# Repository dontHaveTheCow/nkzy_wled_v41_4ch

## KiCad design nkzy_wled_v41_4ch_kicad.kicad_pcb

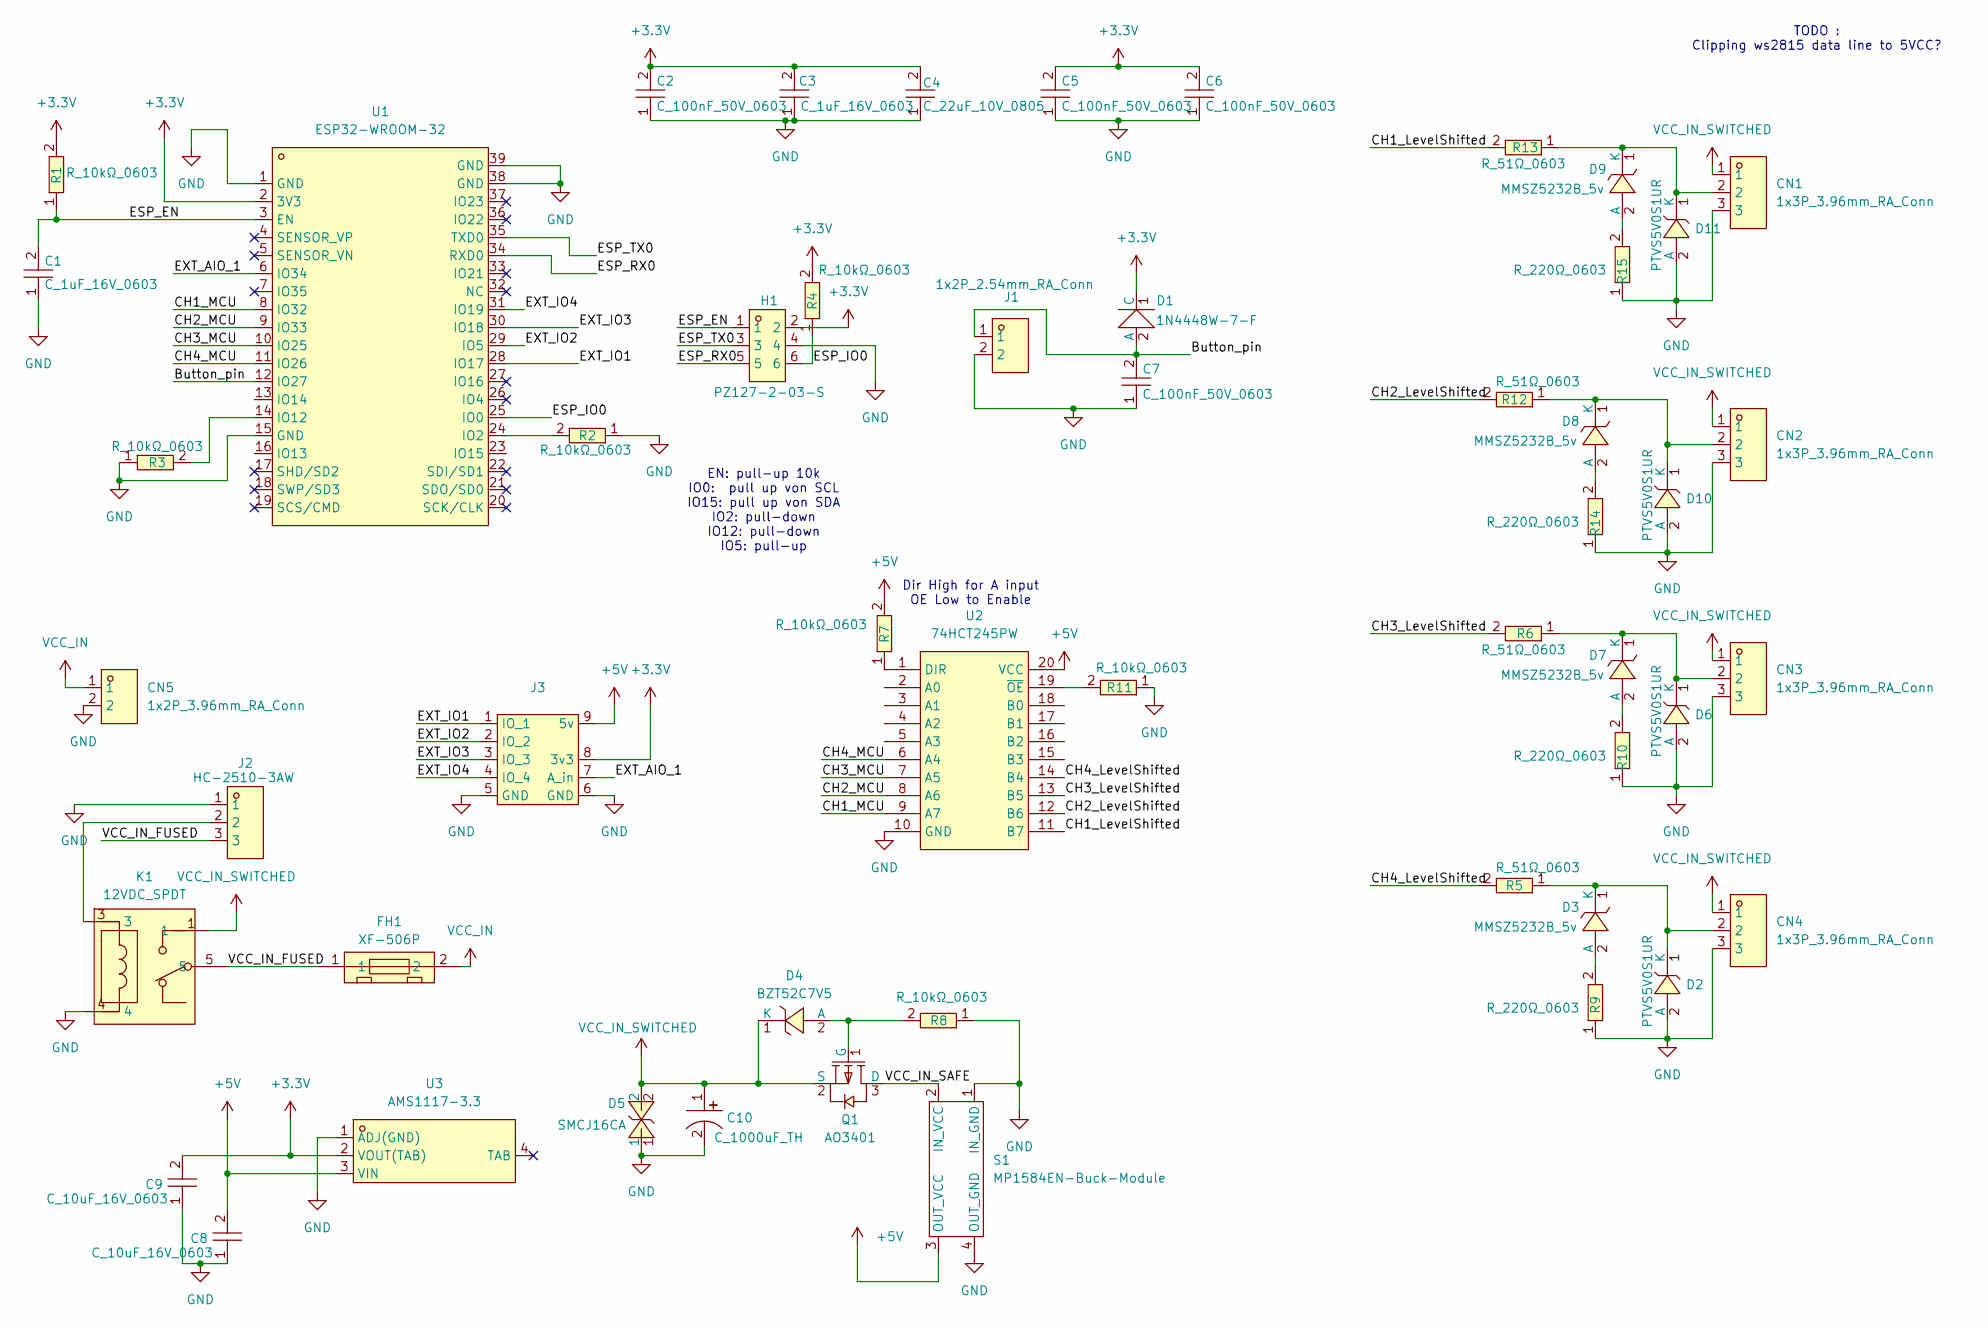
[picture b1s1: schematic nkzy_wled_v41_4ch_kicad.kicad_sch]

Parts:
C1, C3: C_1uF_16V_0603; C0603; Mfr. PartNo CL10A105KO8NNNC; LCSC Part C1592
C2, C5, C6, C7: C_100nF_50V_0603; C0603; Mfr. PartNo 0603B104K500NT; LCSC Part C30926
C4: C_22uF_10V_0805; C0805; Mfr. PartNo CL21A226MPQNNNE; LCSC Part C29277
C8, C9: C_10uF_16V_0603; C0603; Mfr. PartNo CL10A106MO8NQNC; LCSC Part C92487
C10: C_1000uF_TH; CAP-TH_BD10.0-P5.00-D1.0-FD; Mfr. PartNo 01EC4294SHC1000UF25V; LCSC Part C503217
CN1, CN2, CN3, CN4: 1x3P_3.96mm_RA_Conn; CONN-TH_3P-P3.96_HCTL_HC-VH-3A3W; Mfr. PartNo HC-VH-3A3W; LCSC Part C2845760
CN5: 1x2P_3.96mm_RA_Conn; CONN-TH_2P-P3.96_HCTL_HC-VH-2A2W-L; Mfr. PartNo HC-VH-2A2W-L; LCSC Part C2979575
D1: 1N4448W-7-F; SOD-123_L2.8-W1.8-LS3.7-RD; Mfr. PartNo 1N4448W-7-F; LCSC Part C124191
D2, D6, D10, D11: PTVS5V0S1UR; SOD-123FL_L2.7-W1.8-LS3.8-RD; Mfr. PartNo PTVS5V0S1UR; LCSC Part C5380694
D3, D7, D8, D9: MMSZ5232B_5v; SOD-123_L2.7-W1.6-LS3.7-RD; Mfr. PartNo MMSZ5232B; LCSC Part C19077423
D4: BZT52C7V5; SOD-123_L2.7-W1.6-LS3.7-RD; Mfr. PartNo BZT52C7V5; LCSC Part C19077405
D5: SMCJ16CA; DO-214AB_L6.9-W5.9-LS7.9-BI; Mfr. PartNo SMCJ16CA; LCSC Part C41411764
FH1: XF-506P; FUSE-TH_XF-506P; Mfr. PartNo XF-506P; LCSC Part C492610
H1: PZ127-2-03-S; HDR-SMD_6P-P1.27-V-M-R2-C3-LS5.3; Mfr. PartNo PZ127-2-03-S; LCSC Part C3975186
J1: 1x2P_2.54mm_RA_Conn; CONN-TH_2P-P2.54_HCTL_HC-2510-2AW; Mfr. PartNo HC-2510-2AW; LCSC Part C2982041
J2: HC-2510-3AW; CONN-TH_3P-P2.54_HCTL_HC-2510-3AW; Mfr. PartNo HC-2510-3AW; LCSC Part C2982042
J3: nkzy_addon_footprint
K1: 12VDC_SPDT; RELAY-TH_SRA-X-CX; Mfr. PartNo SRA-12VDC-CL; LCSC Part C60169
Q1: AO3401; SOT-23-3_L2.9-W1.4-P1.90-LS2.6-BR; Mfr. PartNo AO3401; LCSC Part C727156
R1, R2, R3, R4, R7, R8, R11: R_10kΩ_0603; R0603; Mfr. PartNo 0603WAF1002T5E; LCSC Part C25804
R5, R6, R12, R13: R_51Ω_0603; R0603; Mfr. PartNo 0603WAF510JT5E; LCSC Part C23197
R9, R10, R14, R15: R_220Ω_0603; R0603; Mfr. PartNo 0603WAF2200T5E; LCSC Part C22962
S1: MP1584EN-Buck-Module
U1: ESP32-WROOM-32; WIFIM-SMD_ESP32-WROOM-32-N4; Mfr. PartNo ESP32-WROOM-32; LCSC Part C82899
U2: 74HCT245PW; TSSOP-20_L6.5-W4.4-P0.65-LS6.4-BL; Mfr. PartNo 74HCT245PW; LCSC Part C5980
U3: AMS1117-3.3; SOT-223-4_L6.5-W3.5-P2.30-LS7.0-BR; Mfr. PartNo AMS1117-3.3_C347222; LCSC Part C347222

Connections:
+3.3V: C2.2, C3.2, C4.2, C5.2, C6.2, C9.2, D1.1 (C), H1.2, J3.8 (3v3), R1.2, R4.2, U1.2 (3V3), U3.2 (VOUT(TAB))
+5V: C8.2, J3.9 (5v), R7.2, S1.3 (OUT_VCC), U2.20 (VCC), U3.3 (VIN)
/Button_pin: C7.2, D1.2 (A), J1.1, U1.12 (IO27)
/CH1_LevelShifted: R13.2, U2.11 (B7)
/CH1_MCU: U1.8 (IO32), U2.9 (A7)
/CH2_LevelShifted: R12.2, U2.12 (B6)
/CH2_MCU: U1.9 (IO33), U2.8 (A6)
/CH3_LevelShifted: R6.2, U2.13 (B5)
/CH3_MCU: U1.10 (IO25), U2.7 (A5)
/CH4_LevelShifted: R5.2, U2.14 (B4)
/CH4_MCU: U1.11 (IO26), U2.6 (A4)
/ESP_EN: C1.2, H1.1, R1.1, U1.3 (EN)
/ESP_IO0: H1.6, R4.1, U1.25 (IO0)
/ESP_RX0: H1.5, U1.34 (RXD0)
/ESP_TX0: H1.3, U1.35 (TXD0)
/EXT_AIO_1: J3.7 (A_in), U1.6 (IO34)
/EXT_IO1: J3.1 (IO_1), U1.28 (IO17)
/EXT_IO2: J3.2 (IO_2), U1.29 (IO5)
/EXT_IO3: J3.3 (IO_3), U1.30 (IO18)
/EXT_IO4: J3.4 (IO_4), U1.31 (IO19)
/VCC_IN_FUSED: FH1.1, J2.3, K1.5
/VCC_IN_SAFE: Q1.3 (D), S1.2 (IN_VCC)
GND: C1.1, C2.1, C3.1, C4.1, C5.1, C6.1, C7.1, C8.1, C9.1, C10.2, CN1.3, CN2.3, CN3.3, CN4.3, CN5.2, D2.2 (A), D5.1, D6.2 (A), D10.2 (A), D11.2 (A), H1.4, J1.2, J2.1, J3.5 (GND), J3.6 (GND), K1.4, R2.1, R3.1, R8.1, R9.1, R10.1, R11.1, R14.1, R15.1, S1.1 (IN_GND), S1.4 (OUT_GND), U1.1 (GND), U1.15 (GND), U1.38 (GND), U1.39 (GND), U2.10 (GND), U3.1 (ADJ(GND))
unnamed: CN4.2, D2.1 (K), D3.1 (K), R5.1
unnamed: D3.2 (A), R9.2
unnamed: D4.2 (A), Q1.1 (G), R8.2
unnamed: CN3.2, D6.1 (K), D7.1 (K), R6.1
unnamed: D7.2 (A), R10.2
unnamed: D8.2 (A), R14.2
unnamed: D9.2 (A), R15.2
unnamed: CN2.2, D8.1 (K), D10.1 (K), R12.1
unnamed: CN1.2, D9.1 (K), D11.1 (K), R13.1
unnamed: J2.2, K1.3
unnamed: R2.2, U1.24 (IO2)
unnamed: R3.2, U1.14 (IO12)
unnamed: R7.1, U2.1 (DIR)
unnamed: R11.2, U2.19 (~OE)
VCC_IN: CN5.1, FH1.2
VCC_IN_SWITCHED: C10.1, CN1.1, CN2.1, CN3.1, CN4.1, D4.1 (K), D5.2, K1.1, Q1.2 (S)

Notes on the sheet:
Dir High for A input OE Low to Enable
TODO : Clipping ws2815 data line to 5VCC?
EN: pull-up 10k IO0: pull up von SCL IO15: pull up von SDA IO2: pull-down IO12: pull-down IO5: pull-up

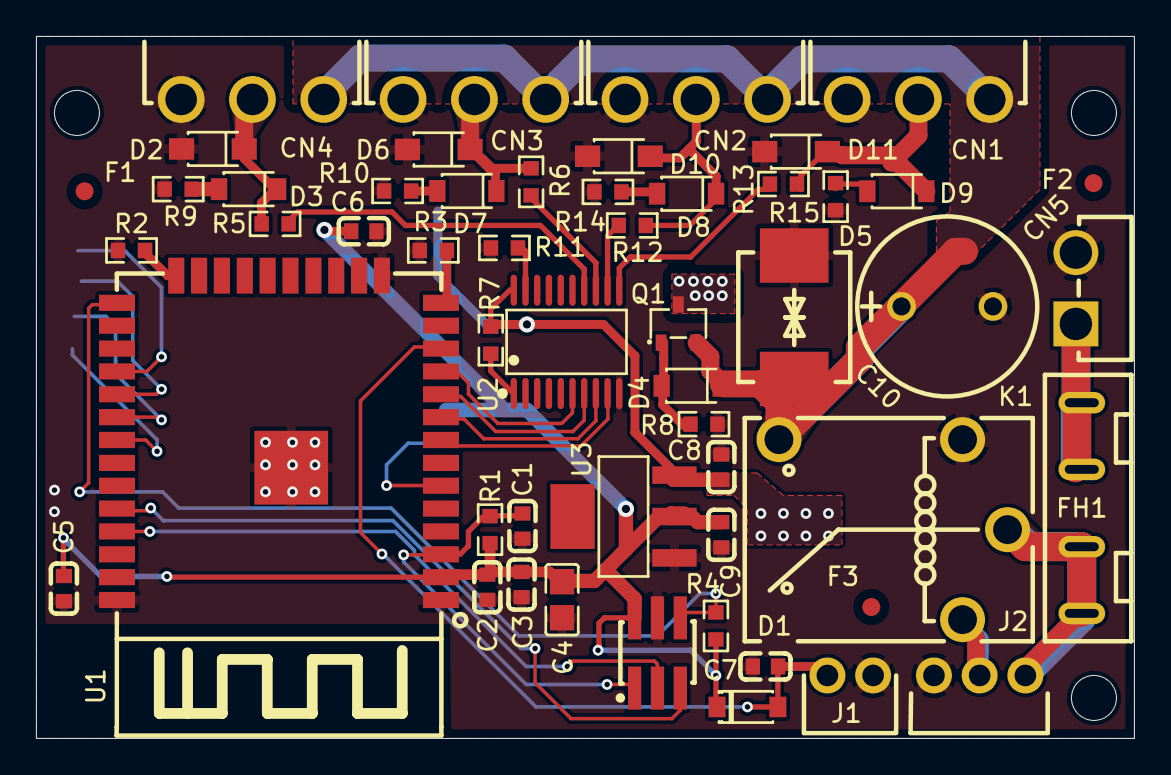
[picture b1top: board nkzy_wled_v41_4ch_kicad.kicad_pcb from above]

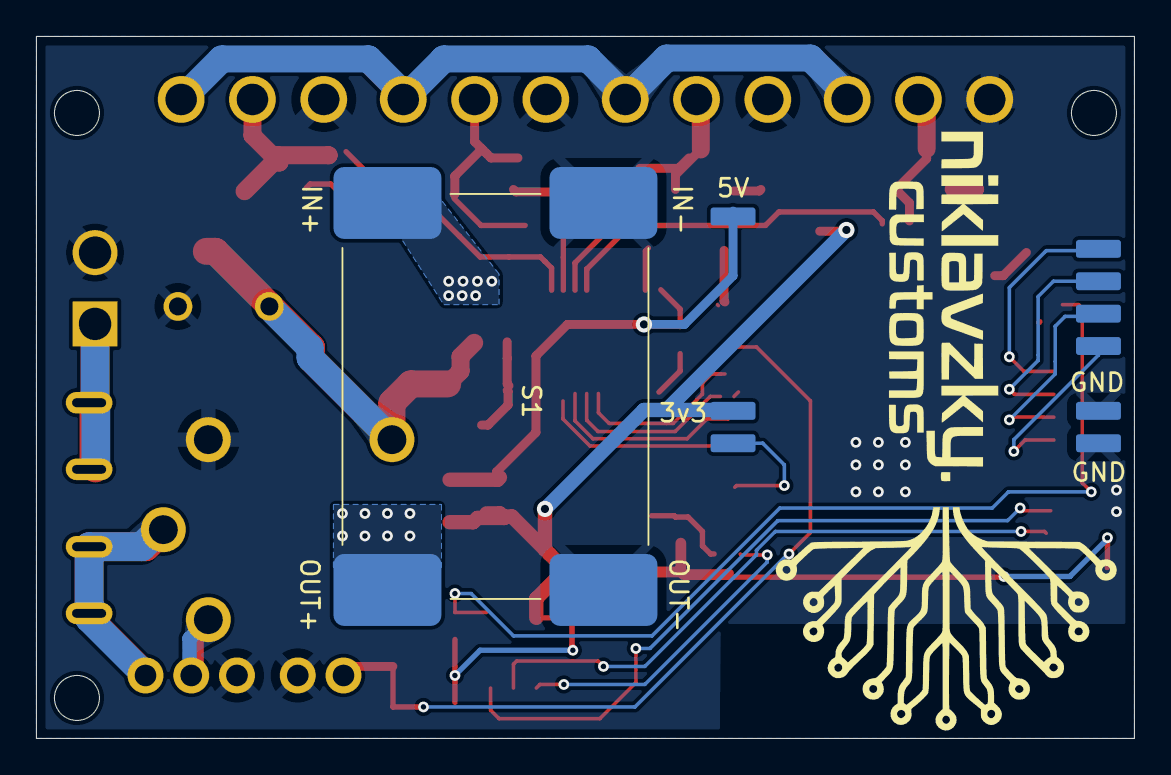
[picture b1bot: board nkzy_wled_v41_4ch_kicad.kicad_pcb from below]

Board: 2 copper layers, 61.0 x 39.0 mm, 55 parts (2 on the bottom side), 39 nets.

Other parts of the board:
F1, F2, F3: Fiducial_1mm_Mask2mm

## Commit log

2025-12-18 Routed 4 ch pcb and resolved all DRC
